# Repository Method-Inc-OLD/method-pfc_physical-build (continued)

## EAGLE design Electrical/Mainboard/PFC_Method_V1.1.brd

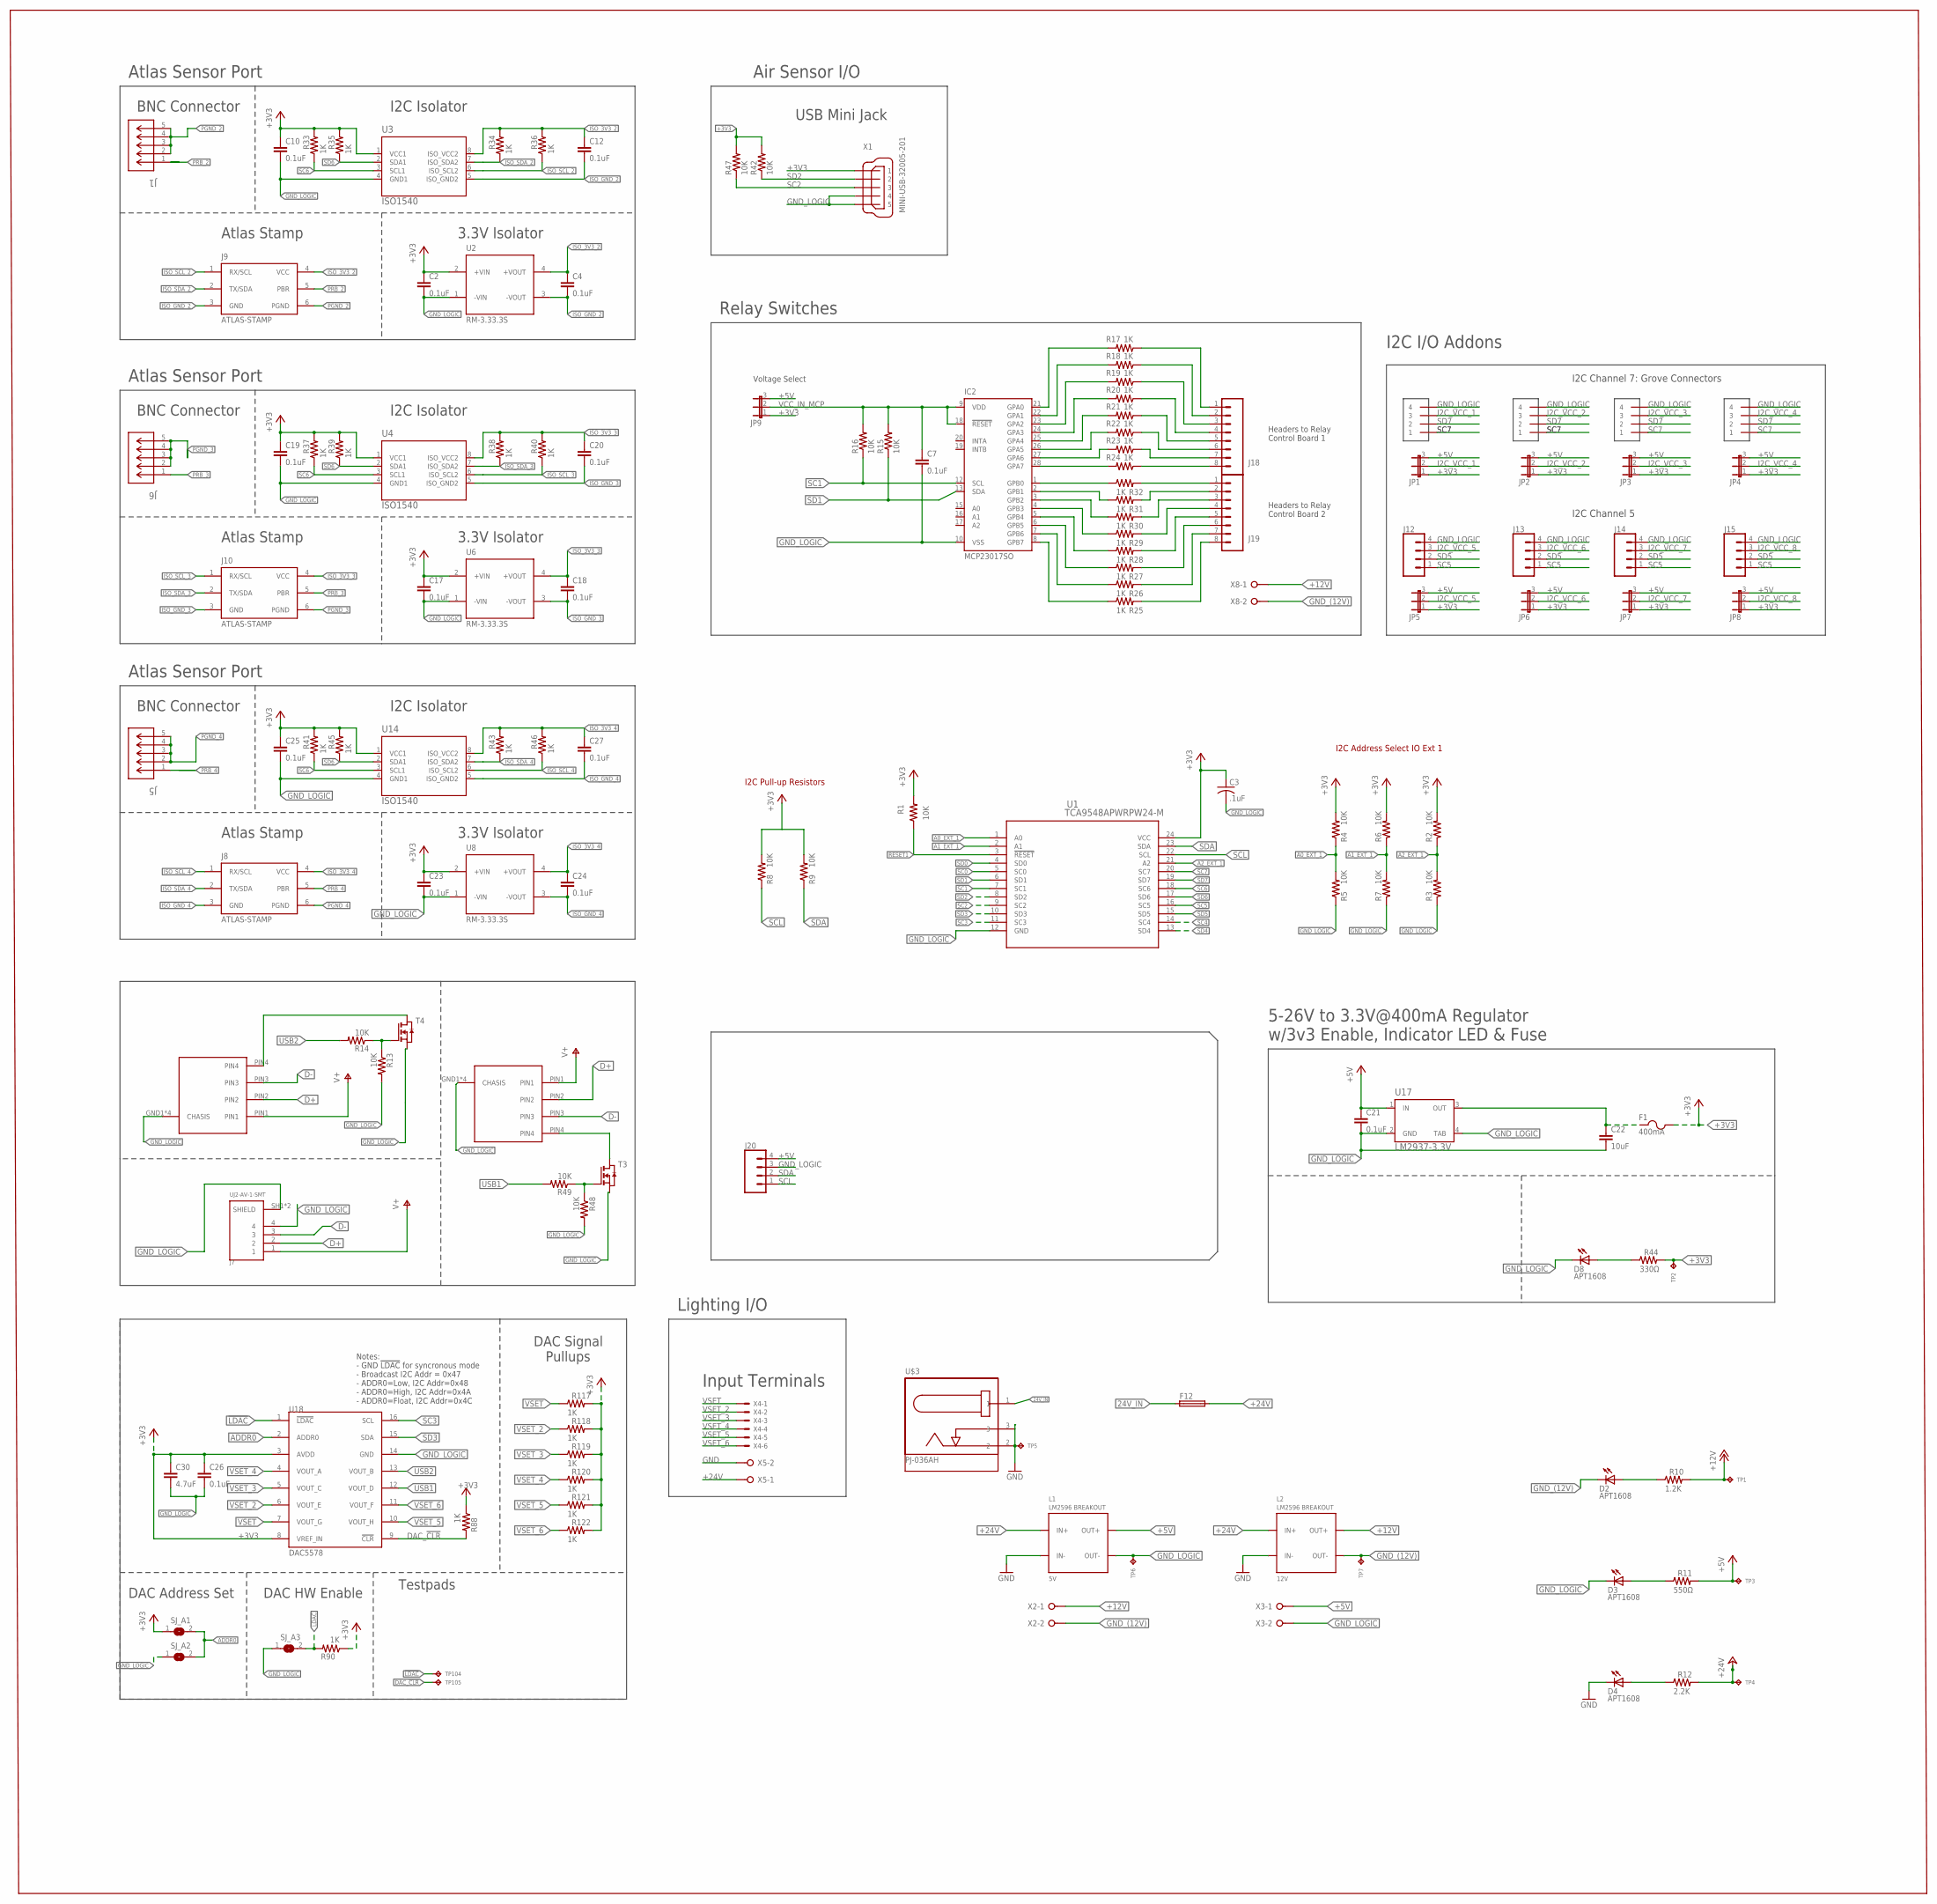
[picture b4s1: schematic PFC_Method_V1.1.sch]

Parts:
C2, C4, C7, C10, C12, C17, C18, C19, C20, C21, C23, C24, C25, C26, C27: 0.1uF; C0603
C3: .1uF; C0603@1
C22: 10uF; C0805
C30: 4.7uF; C0805
D2, D3, D4, D8: APT1608; CHIPLED_0603
F1: 400mA; 0603
F12: GSH15
IC2: MCP23017SO; SO28W
J1, J5, J6: 5-1634503-1; CONN5_5-1634503-1
J2, J3, J16, J17: GROVE_4PIN_CONNECTOR
J7: UJ2-AV-1-SMT; CUI_UJ2-AV-1-SMT
J8, J9, J10: ATLAS-STAMP
J12, J13, J14, J15, J20: CONN_04; 1X04
J18, J19: CONN_08"; 1X08
JP1, JP2, JP3, JP4, JP5, JP6, JP7, JP8, JP9: JP2E; JP2
L1: 5V; LM2596
L2: 12V; LM2596
R1, R15, R16, R42, R47: 10K; R0603
R2, R3, R4, R5, R6, R7, R8, R9: 10K; 0603-RES
R10: 1.2K; RC0603N
R11: 550Ω; RC0603N
R12: 2.2K; RC0603N
R13, R14, R48, R49: 10K; R0805W
R17, R18, R19, R20, R21, R22, R23, R24, R25, R26, R27, R28, R29, R30, R31, R32, R33, R34, R35, R36, R37, R38, R39, R40, R41, R43, R45, R46, R88, R90, R117, R118, R119, R120, R121, R122: 1K; RC0603N
R44: 330Ω; RC0603N
SJ_A1, SJ_A2, SJ_A3: SOLDERJUMPERREFLOW_NOPASTE; SJ1
T3, T4: NMOSSOT23; SOT-23
TP1, TP3, TP4, TP5, TP6, TP7, TP104, TP105: TPTP04R; TP04R
TP2: TPTP06R; TP06R
U1: TCA9548APWRPW24-M; PW24-M
U2, U6, U8: RM-3.33.3S; RM3.33.3S-SIP4
U3, U4, U14: ISO1540; D8
U17: LM2937-3.3V; MP04A
U18: DAC5578; TSSOP16
U$3: PJ-036AH; BARREL-JACK-PJ-036AH
U$5, U$6: USB_RIGHT
X1: MINI-USB-32005-201; 32005-201
X2, X3, X5, X8: W237-02P; W237-132
X4: 22-23-2061

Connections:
24V_IN: F12.1, U$3.1
!LDAC!: R90.2, SJ_A3.2, TP104.1, U18.1 (!LDAC!)
+3V3: C2.1, C3.1, C10.1, C17.1, C19.1, C23.1, C25.1, C26.1, C30.1, F1.2, JP1.1, JP2.1, JP3.1, JP4.1, JP5.1, JP6.1, JP7.1, JP8.1, JP9.1, R1.2, R2.2, R4.2, R6.2, R8.2, R9.2, R33.2, R35.2, R37.2, R39.2, R41.2, R42.2, R44.2, R45.2, R47.2, R88.1, R90.1, R117.2, R118.2, R119.2, R120.2, R121.2, R122.2, SJ_A1.1, TP2.TP, U1.24 (VCC), U2.2 (+VIN), U3.1 (VCC1), U4.1 (VCC1), U6.2 (+VIN), U8.2 (+VIN), U14.1 (VCC1), U18.3 (AVDD), U18.8 (VREF_IN), X1.1
+5V: C21.1, J20.4, JP1.3, JP2.3, JP3.3, JP4.3, JP5.3, JP6.3, JP7.3, JP8.3, JP9.3, L1.OUT+, R11.2, TP3.1, U17.1 (IN), X3.1
+12V: L2.OUT+, R10.2, TP1.1, X2.1, X8.1
+24V: F12.2, L1.IN+, L2.IN+, R12.2, TP4.1, X5.1
A0_EXT_1: R4.1, R5.2, U1.1 (A0)
A1_EXT_1: R6.1, R7.2, U1.2 (A1)
A2_EXT_1: R2.1, R3.2, U1.21 (A2)
ADDR0: SJ_A1.2, SJ_A2.2, U18.2 (ADDR0)
D+: J7.2, U$5.PIN2, U$6.PIN2
D-: J7.3, U$5.PIN3, U$6.PIN3
DAC_!CLR!: R88.2, TP105.1, U18.9 (!CLR!)
GND: D4.C, L1.IN-, L2.IN-, TP5.1, U$3.2, U$3.3, X5.2
GND_(12V): D2.C, L2.OUT-, TP7.1, X2.2, X8.2
GND_LOGIC: C2.2, C3.2, C7.2, C10.2, C17.2, C19.2, C21.2, C22.2, C23.2, C25.2, C26.2, C30.2, D3.C, D8.C, IC2.10 (VSS), J2.P$4 (4), J3.P$4 (4), J7.4, J7.SH1 (SHIELD), J7.SH2 (SHIELD), J12.4, J13.4, J14.4, J15.4, J16.P$4 (4), J17.P$4 (4), J20.3, L1.OUT-, R3.1, R5.1, R7.1, R13.2, R48.2, SJ_A2.1, SJ_A3.1, T3.2 (S), T4.2 (S), TP6.1, U1.12 (GND), U2.1 (-VIN), U3.4 (GND1), U4.4 (GND1), U6.1 (-VIN), U8.1 (-VIN), U14.4 (GND1), U17.2 (GND), U17.4 (TAB), U18.14 (GND), U$5.GND1 (CHASIS), U$5.GND2 (CHASIS), U$5.GND3 (CHASIS), U$5.GND4 (CHASIS), U$6.GND1 (CHASIS), U$6.GND2 (CHASIS), U$6.GND3 (CHASIS), U$6.GND4 (CHASIS), X1.4, X1.5, X3.2
I2C_VCC_1: J16.P$3 (3), JP1.2
I2C_VCC_2: J17.P$3 (3), JP2.2
I2C_VCC_3: J2.P$3 (3), JP3.2
I2C_VCC_4: J3.P$3 (3), JP4.2
I2C_VCC_5: J12.3, JP5.2
I2C_VCC_6: J13.3, JP6.2
I2C_VCC_7: J14.3, JP7.2
I2C_VCC_8: J15.3, JP8.2
ISO_3V3_2: C4.1, C12.1, J9.4 (VCC), R34.2, R36.2, U2.4 (+VOUT), U3.8 (ISO_VCC2)
ISO_3V3_3: C18.1, C20.1, J10.4 (VCC), R38.2, R40.2, U4.8 (ISO_VCC2), U6.4 (+VOUT)
ISO_3V3_4: C24.1, C27.1, J8.4 (VCC), R43.2, R46.2, U8.4 (+VOUT), U14.8 (ISO_VCC2)
ISO_GND_2: C4.2, C12.2, J9.3 (GND), U2.3 (-VOUT), U3.5 (ISO_GND2)
ISO_GND_3: C18.2, C20.2, J10.3 (GND), U4.5 (ISO_GND2), U6.3 (-VOUT)
ISO_GND_4: C24.2, C27.2, J8.3 (GND), U8.3 (-VOUT), U14.5 (ISO_GND2)
ISO_SCL_2: J9.1 (RX/SCL), R36.1, U3.6 (ISO_SCL2)
ISO_SCL_3: J10.1 (RX/SCL), R40.1, U4.6 (ISO_SCL2)
ISO_SCL_4: J8.1 (RX/SCL), R46.1, U14.6 (ISO_SCL2)
ISO_SDA_2: J9.2 (TX/SDA), R34.1, U3.7 (ISO_SDA2)
ISO_SDA_3: J10.2 (TX/SDA), R38.1, U4.7 (ISO_SDA2)
ISO_SDA_4: J8.2 (TX/SDA), R43.1, U14.7 (ISO_SDA2)
unnamed: R13.1, R14.1, T4.3 (G)
unnamed: D3.A, R11.1
unnamed: R48.1, R49.1, T3.3 (G)
unnamed: D4.A, R12.1
unnamed: T3.1 (D), U$6.PIN4
unnamed: IC2.21 (GPA0), R17.2
unnamed: IC2.22 (GPA1), R18.2
unnamed: T4.1 (D), U$5.PIN4
unnamed: IC2.23 (GPA2), R19.2
unnamed: IC2.24 (GPA3), R20.2
unnamed: IC2.25 (GPA4), R21.2
unnamed: D2.A, R10.1
unnamed: IC2.26 (GPA5), R22.2
unnamed: IC2.27 (GPA6), R23.2
unnamed: IC2.28 (GPA7), R24.2
unnamed: J18.1, R17.1
unnamed: J18.2, R18.1
unnamed: J18.3, R19.1
unnamed: J18.4, R20.1
unnamed: J18.5, R21.1
unnamed: J18.6, R22.1
unnamed: J18.7, R23.1
unnamed: J18.8, R24.1
unnamed: J19.8, R25.2
unnamed: J19.7, R26.2
unnamed: J19.6, R27.2
unnamed: J19.5, R28.2
unnamed: J19.4, R29.2
unnamed: J19.3, R30.2
unnamed: J19.2, R31.2
unnamed: J19.1, R32.2
unnamed: IC2.8 (GPB7), R25.1
unnamed: IC2.7 (GPB6), R26.1
unnamed: IC2.6 (GPB5), R27.1
unnamed: IC2.5 (GPB4), R28.1
unnamed: IC2.4 (GPB3), R29.1
unnamed: IC2.3 (GPB2), R30.1
unnamed: IC2.2 (GPB1), R31.1
unnamed: IC2.1 (GPB0), R32.1
unnamed: D8.A, R44.1
unnamed: C22.1, F1.1, U17.3 (OUT)
PGND_2: J1.2, J1.3, J1.4, J1.5, J9.6 (PGND)
PGND_3: J6.2, J6.3, J6.4, J6.5, J10.6 (PGND)
PGND_4: J5.2, J5.3, J5.4, J5.5, J8.6 (PGND)
PRB_2: J1.1, J9.5 (PBR)
PRB_3: J6.1, J10.5 (PBR)
PRB_4: J5.1, J8.5 (PBR)
RESET1: R1.1, U1.3 (!RESET)
SC0: U1.5 (SC0)
SC1: IC2.12 (SCL), R16.1, U1.7 (SC1)
SC2: R47.1, U1.9 (SC2), X1.3
SC3: U1.11 (SC3), U18.16 (SCL)
SC4: U1.14 (SC4)
SC5: J12.1, J13.1, J14.1, J15.1, U1.16 (SC5)
SC6: R33.1, R37.1, R41.1, U1.18 (SC6), U3.3 (SCL1), U4.3 (SCL1), U14.3 (SCL1)
SC7: J2.P$1 (1), J3.P$1 (1), J16.P$1 (1), J17.P$1 (1), U1.20 (SC7)
SCL: J20.1, R8.1, U1.22 (SCL)
SD0: U1.4 (SD0)
SD1: IC2.13 (SDA), R15.1, U1.6 (SD1)
SD2: R42.1, U1.8 (SD2), X1.2
SD3: U1.10 (SD3), U18.15 (SDA)
SD4: U1.13 (SD4)
SD5: J12.2, J13.2, J14.2, J15.2, U1.15 (SD5)
SD6: R35.1, R39.1, R45.1, U1.17 (SD6), U3.2 (SDA1), U4.2 (SDA1), U14.2 (SDA1)
SD7: J2.P$2 (2), J3.P$2 (2), J16.P$2 (2), J17.P$2 (2), U1.19 (SD7)
SDA: J20.2, R9.1, U1.23 (SDA)
USB1: R49.2, U18.12 (VOUT_D)
USB2: R14.2, U18.13 (VOUT_B)
V+: J7.1, U$5.PIN1, U$6.PIN1
VCC_IN_MCP: C7.1, IC2.9 (VDD), IC2.18 (!RESET), JP9.2, R15.2, R16.2
VSET: R117.1, U18.7 (VOUT_G), X4.1
VSET_2: R118.1, U18.6 (VOUT_E), X4.2
VSET_3: R119.1, U18.5 (VOUT_C), X4.3
VSET_4: R120.1, U18.4 (VOUT_A), X4.4
VSET_5: R121.1, U18.10 (VOUT_H), X4.5
VSET_6: R122.1, U18.11 (VOUT_F), X4.6

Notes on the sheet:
I2C Pull-up Resistors
I2C Address Select IO Ext 1
5-26V to 3.3V@400mA Regulator w/3v3 Enable, Indicator LED & Fuse
Notes: - GND !LDAC! for syncronous mode - Broadcast I2C Addr = 0x47 - ADDR0=Low, I2C Addr=0x48 - ADDR0=High, I2C Addr=0x4A - ADDR0=Float, I2C Addr=0x4C
Testpads
DAC Signal Pullups
DAC Address Set
DAC HW Enable
3.3V Isolator
I2C Isolator
Atlas Stamp
BNC Connector
Atlas Sensor Port
Air Sensor I/O
USB Mini Jack
Input Terminals
Lighting I/O
Relay Switches
I2C I/O Addons
I2C Channel 7: Grove Connectors
I2C Channel 5
Headers to Relay Control Board 1
Headers to Relay Control Board 2
Voltage Select

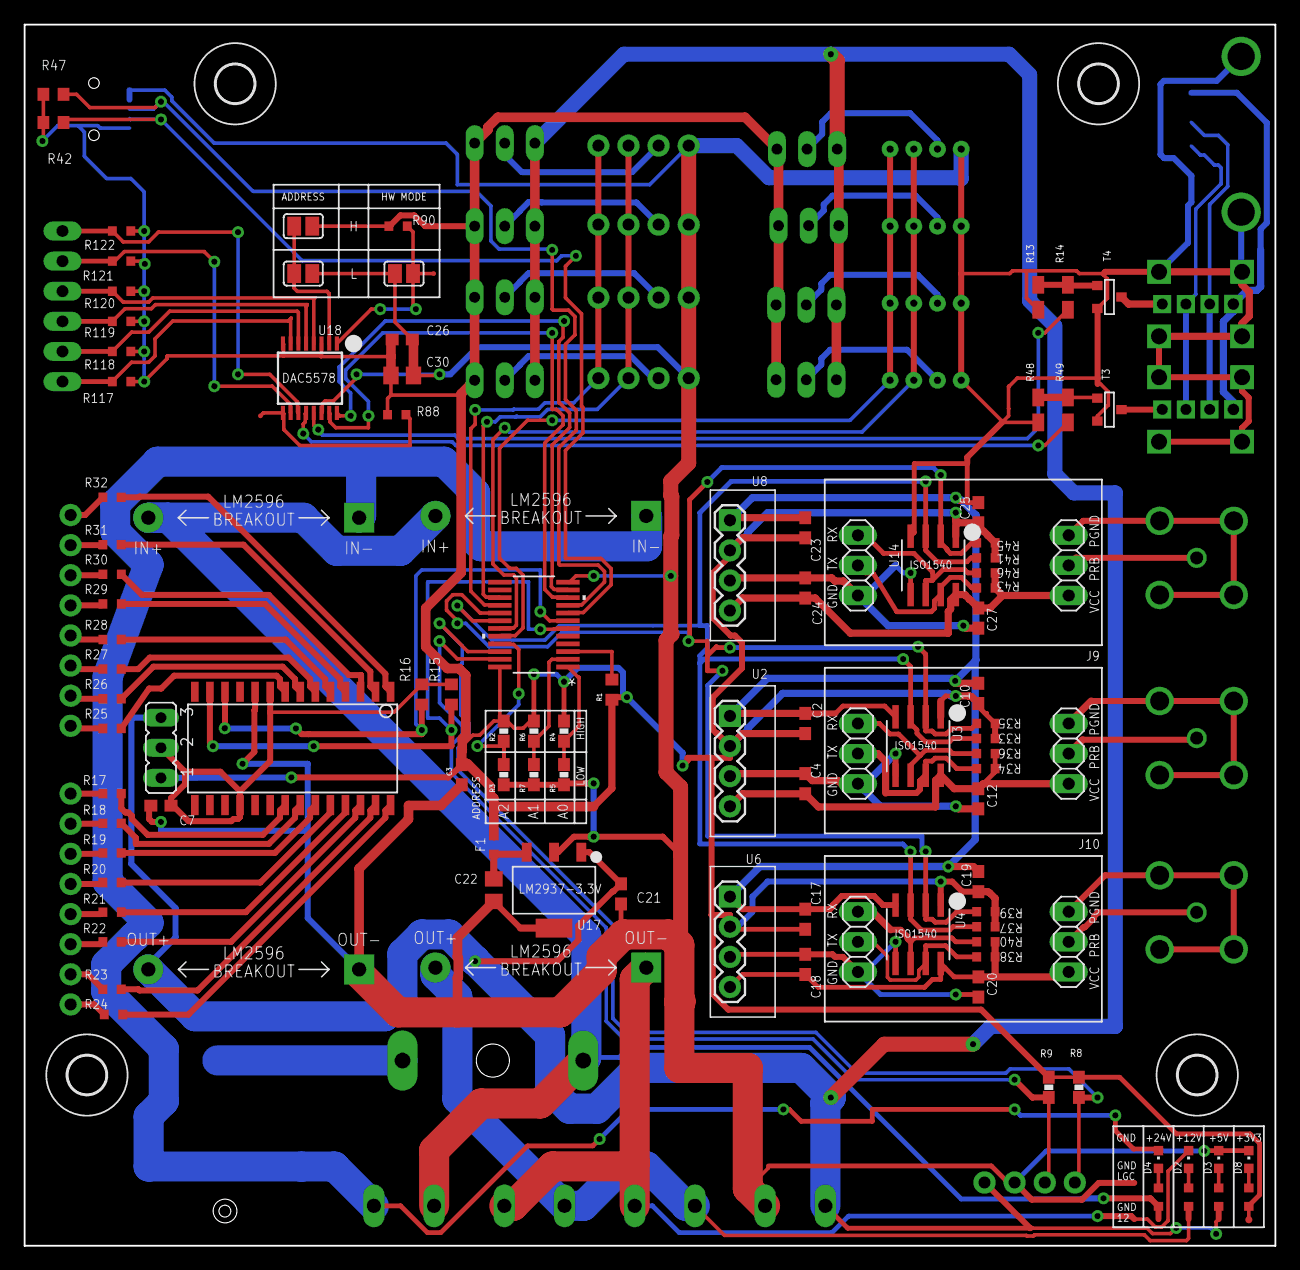
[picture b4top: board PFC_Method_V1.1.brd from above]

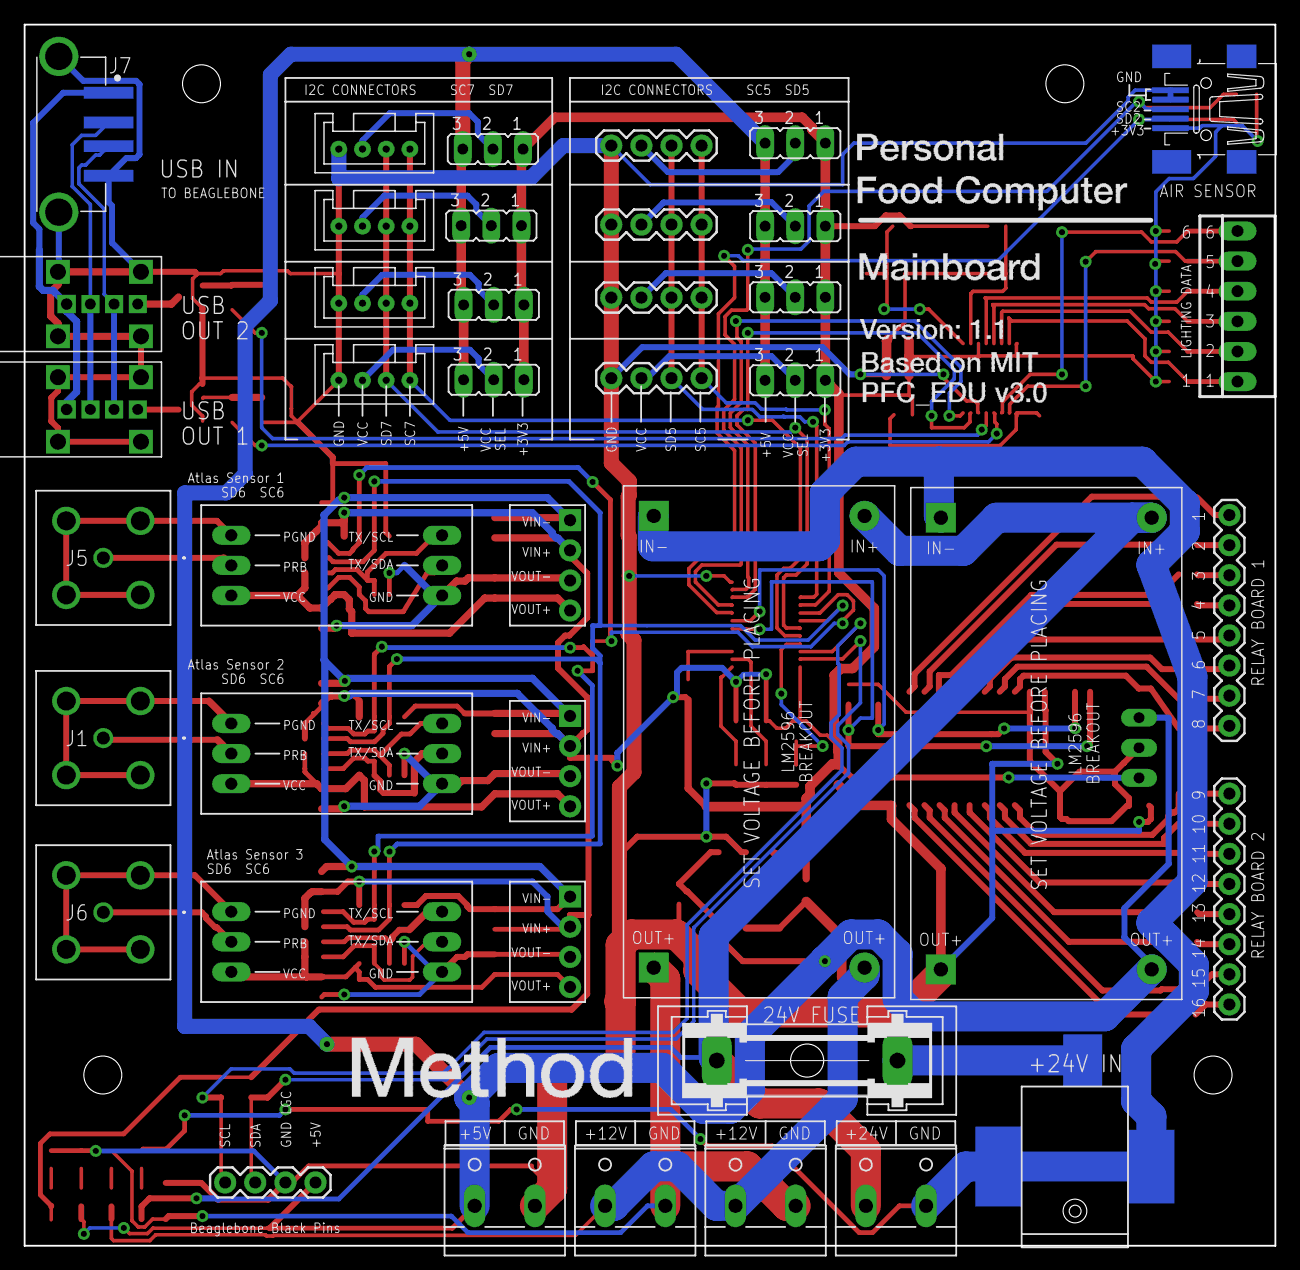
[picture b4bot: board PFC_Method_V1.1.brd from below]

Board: 2 copper layers, 105.5 x 103.0 mm, 147 parts (35 on the bottom side), 108 nets.

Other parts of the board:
U$1, U$2, U$7, U$8: 3,2

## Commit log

2019-05-31 All components in Rhino and STL for printing
2019-06-02 Readme's
2019-06-02 Readme's Fix
2019-06-17 Readme cleanup
2019-06-17 Readme formatting
2019-08-02 Added safety mount
2019-08-02 Electrical
